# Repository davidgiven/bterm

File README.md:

bterm
=====

What?
-----

This is a set of firmware and hardware to turn a Brother WP-1 into a serial
terminal for a Raspberry Pi.

It consists of:

  - software to make a Brother bootable floppy containing a VT102-subset serial
	terminal

  - firmware for a PSoC5 CY8CKIT-049 based interface

  - a PCB which connects the Brother, CY8CKIT-049 and Raspberry Pi together

  - a 3D printable fascia which fits into the Brother's expansion slot

It also provides a MDA/Hercules/CGA-compatible video out connector which
reproduces what's on the Brother's screen.

Why?
----

Why not?

How?
----

So this is all so bespoke to my purposes that it's probably not going to be
very useful to anyone else. What documentation there is comes from the Youtube
series of videos I made while I developed this:

https://www.youtube.com/playlist?list=PLuQ2s_IbSWv5NDpc9Ew3BYDSF7siX9mNj

But here are some quick notes:

  - build the client software are write it to a floppy (you'll need zmac, ld80
	and fluxengine)

  - build the CY8CKIT-049 firmware and flash it with the Cypress development
	tools

  - get the PCB made and solder the connectors onto it

  - solder a 44-pin connector onto the unpopulated expansion breakout pads on
	the Brother motherboard

  - install Linux (or another OS of your choice) onto a Raspberry Pi, and
	configure out to use hardware handshaking on the main UART

  - plug everything together and attach the flyleads to the Brother CPU's /RD,
	/WR and /IOEN lines

  - ensure that there's a reset button and power switch connected to the
	interface board

  - switch everything on with Code+Q pressed on the Brother

...and then, if you're lucky, it might work.

If you are actually interested in trying this, best thing is to [file an
issue](https://github.com/davidgiven/bterm/issues/new/choose) and I'll see what
I can do to help. Or just send me an email (see below).

Who?
----

I am David Given, a.k.a. hjalfi in various places. Feel free to send me email
at [dg@cowlark.com](mailto:dg@cowlark.com). You may also [like to visit my
website](http://cowlark.com); there may or may not be something interesting
there.

License?
--------

Everything I wrote, which is nearly everything, is freely redistributable under
the terms of the simplified 2-clause BSD license. tl;dr: go nuts, just don't
claim you wrote it. See the `LICENSE` file for more details.

The one exception are the Raspberry Pi and CYC8KIT-049 footprints in the
`kicad-pcb` directory, which are by SnapEDA and licensed under a Creative
Commons Attribution-ShareAlike 4.0 International License (CC BY-SA) with Design
Exception 1.0. This exception essentially means that the CC BY-SA limitations
don't apply as they're being distributed as part of an aggregate design. [See
SnapEDA's page for
details.](https://support.snapeda.com/en/articles/2957815-what-is-the-design-exception-1-0)

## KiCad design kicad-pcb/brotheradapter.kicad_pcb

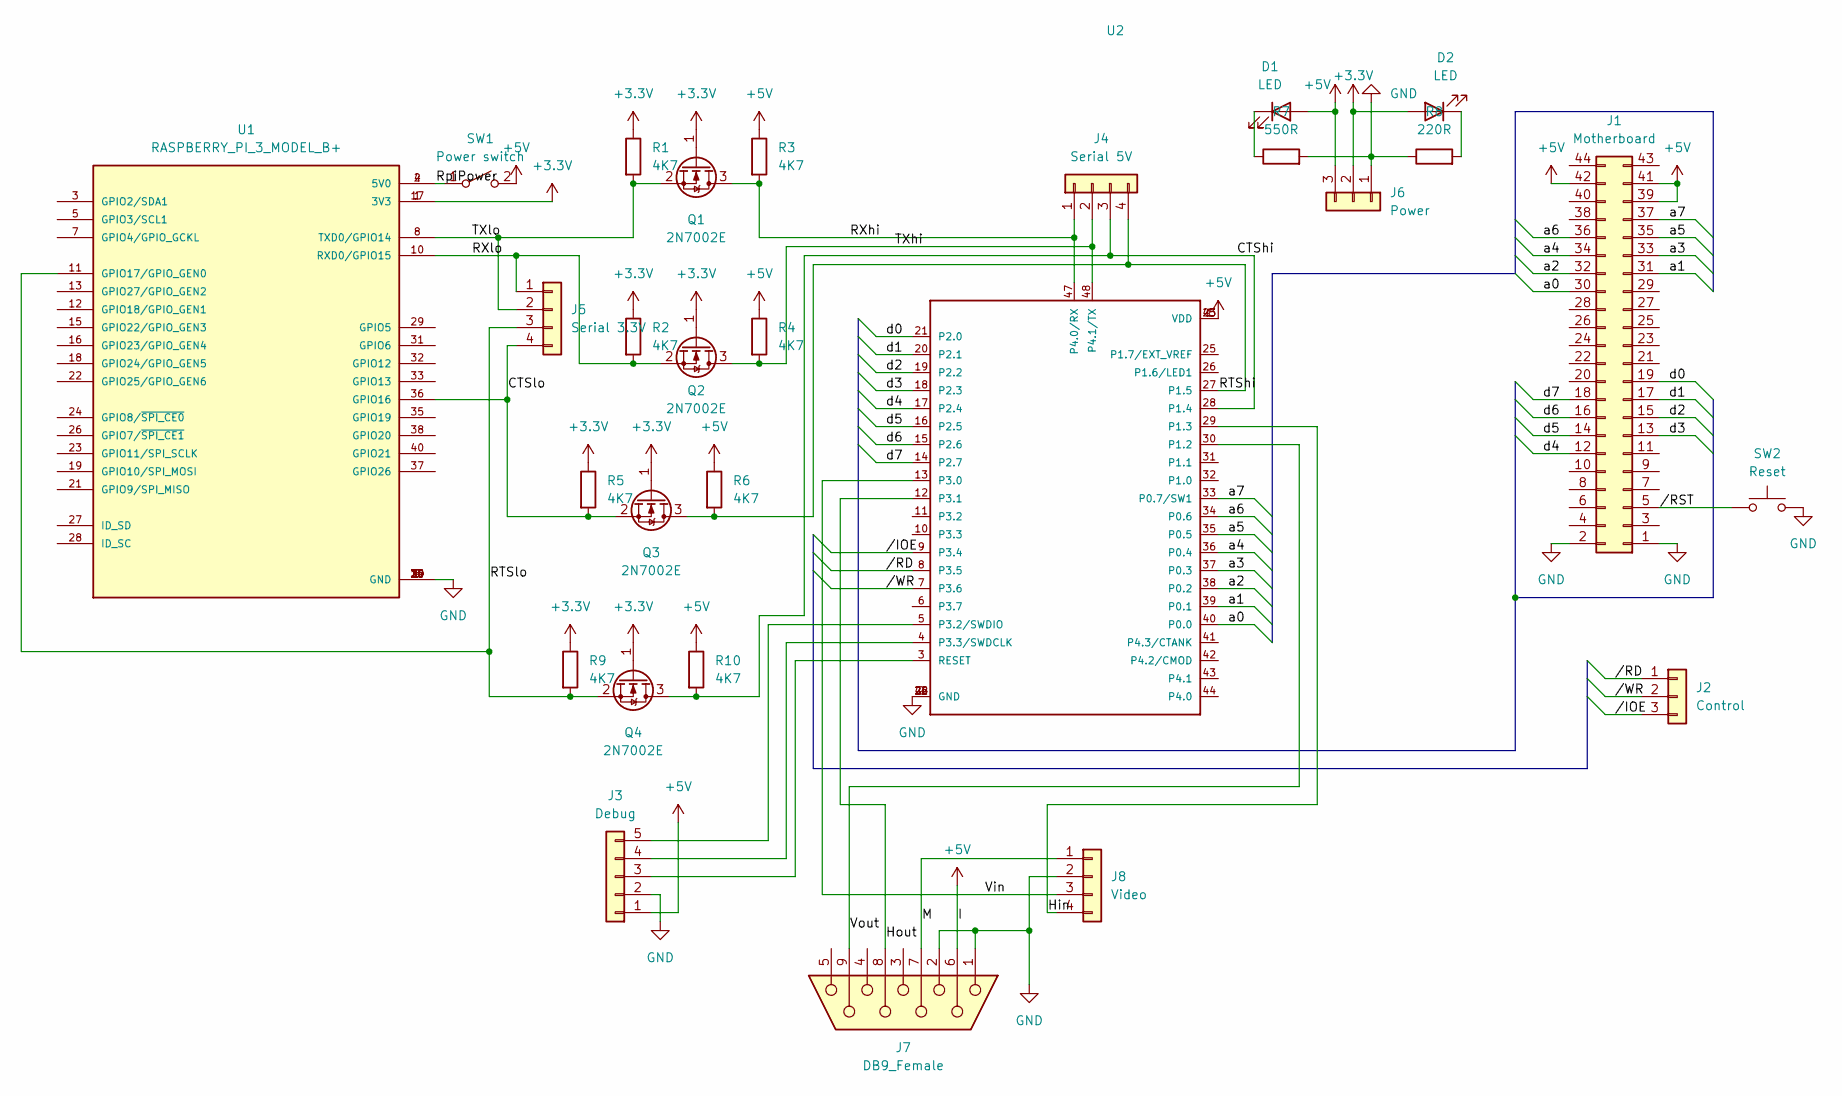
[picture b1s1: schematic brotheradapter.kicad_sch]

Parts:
D1, D2: LED; LED_0603_1608Metric
J1: Motherboard; PinHeader_2x22_P2.54mm_Vertical
J2: Control; PinSocket_1x03_P2.54mm_Vertical
J3: Debug; PinHeader_1x05_P2.54mm_Vertical
J4: Serial 5V; PinSocket_1x04_P2.54mm_Vertical
J5: Serial 3.3V; PinSocket_1x04_P2.54mm_Vertical
J6: Power; PinSocket_1x03_P2.54mm_Vertical
J7: DB9_Female; DSUB-9_Female_EdgeMount_P2.77mm
J8: Video; PinHeader_1x04_P2.54mm_Vertical
Q1, Q2, Q3, Q4: 2N7002E; SOT-23
R1, R2, R3, R4, R5, R6, R9, R10: 4K7; R_0603_1608Metric
R7: 550R; R_0603_1608Metric
R8: 220R; R_0603_1608Metric
SW1: Power switch; PinHeader_1x02_P2.54mm_Vertical
SW2: Reset; PinHeader_1x02_P2.54mm_Vertical
U1: RASPBERRY_PI_3_MODEL_B+; MODULE_RASPBERRY_PI_3_MODEL_B+; PARTREV 1.0
U2: CY8CKIT-049-42XX

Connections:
+3V3: D2.2 (A), J6.2, Q1.1 (G), Q2.1 (G), Q3.1 (G), Q4.1 (G), R1.1, R2.1, R5.1, R9.1, U1.1 (3V3), U1.17 (3V3)
+5V: D1.2 (A), J1.39, J1.41, J1.42, J3.1, J6.3, J7.6, R3.1, R4.1, R6.1, R10.1, SW1.2 (B), U2.1 (VDD), U2.23 (VDD), U2.45 (VDD)
/CTShi: J4.3, Q4.3 (D), R10.2, U2.28 (P1.4)
/CTSlo: J5.4, Q3.2 (S), R5.2, U1.36 (GPIO16)
/Hin: J8.4, U2.29 (P1.3)
/Hout: J7.8, U2.12 (P3.1)
/M: J7.7, J8.1
/RTSlo: J5.3, Q4.2 (S), R9.2, U1.11 (GPIO17/GPIO_GEN0)
/RXhi: J4.1, Q1.3 (D), R3.2, U2.47 (P4.0/RX)
/RXlo: J5.1, Q2.2 (S), R2.2, U1.10 (RXD0/GPIO15)
/RpiPower: SW1.1 (A), U1.2 (5V0), U1.4 (5V0)
/TXhi: J4.2, Q2.3 (D), R4.2, U2.48 (P4.1/TX)
/TXlo: J5.2, Q1.2 (S), R1.2, U1.8 (TXD0/GPIO14)
/Vin: J8.3, U2.13 (P3.0)
/Vout: J7.9, U2.30 (P1.2)
/a0: J1.30, U2.40 (P0.0)
/a1: J1.31, U2.39 (P0.1)
/a2: J1.32, U2.38 (P0.2)
/a3: J1.33, U2.37 (P0.3)
/a4: J1.34, U2.36 (P0.4)
/a5: J1.35, U2.35 (P0.5)
/a6: J1.36, U2.34 (P0.6)
/a7: J1.37, U2.33 (P0.7/SW1)
/d0: J1.19, U2.21 (P2.0)
/d1: J1.17, U2.20 (P2.1)
/d2: J1.15, U2.19 (P2.2)
/d3: J1.13, U2.18 (P2.3)
/d4: J1.12, U2.17 (P2.4)
/d5: J1.14, U2.16 (P2.5)
/d6: J1.16, U2.15 (P2.6)
/d7: J1.18, U2.14 (P2.7)
//IOE: J2.3, U2.9 (P3.4)
//RD: J2.1, U2.8 (P3.5)
//RST: J1.5, SW2.1
//WR: J2.2, U2.7 (P3.6)
GND: J1.1, J1.2, J3.2, J6.1, J7.1, J7.2, J8.2, R7.2, R8.1, SW2.2, U1.6 (GND), U1.9 (GND), U1.14 (GND), U1.20 (GND), U1.25 (GND), U1.30 (GND), U1.34 (GND), U1.39 (GND), U2.2 (GND), U2.22 (GND), U2.24 (GND), U2.46 (GND)
unnamed: D1.1 (K), R7.1
unnamed: D2.1 (K), R8.2
unnamed: J3.3, U2.3 (RESET)
unnamed: J3.4, U2.4 (P3.3/SWDCLK)
unnamed: J3.5, U2.5 (P3.2/SWDIO)
unnamed: J4.4, Q3.3 (D), R6.2, U2.27 (P1.5)

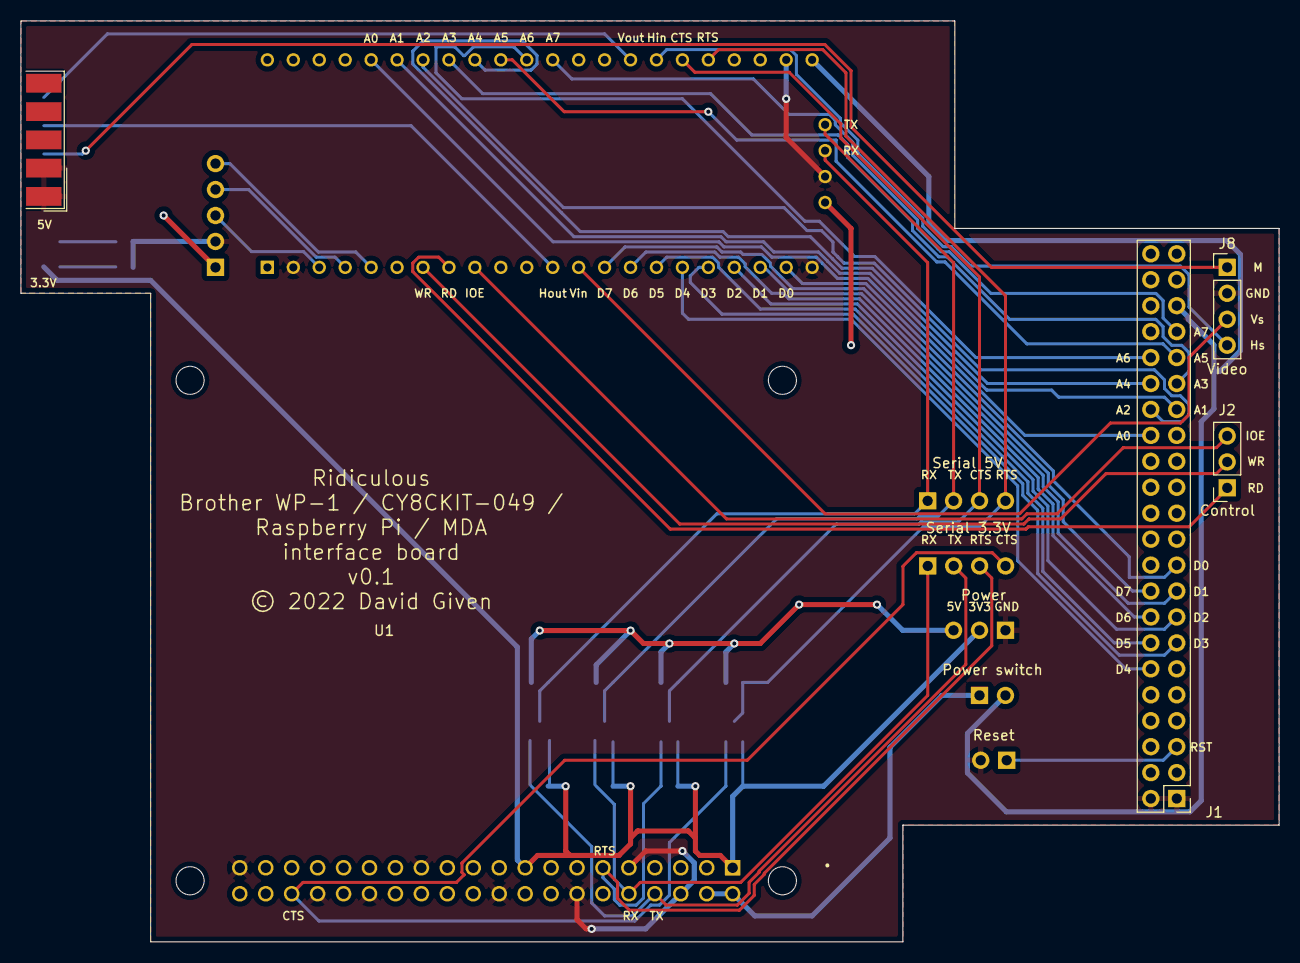
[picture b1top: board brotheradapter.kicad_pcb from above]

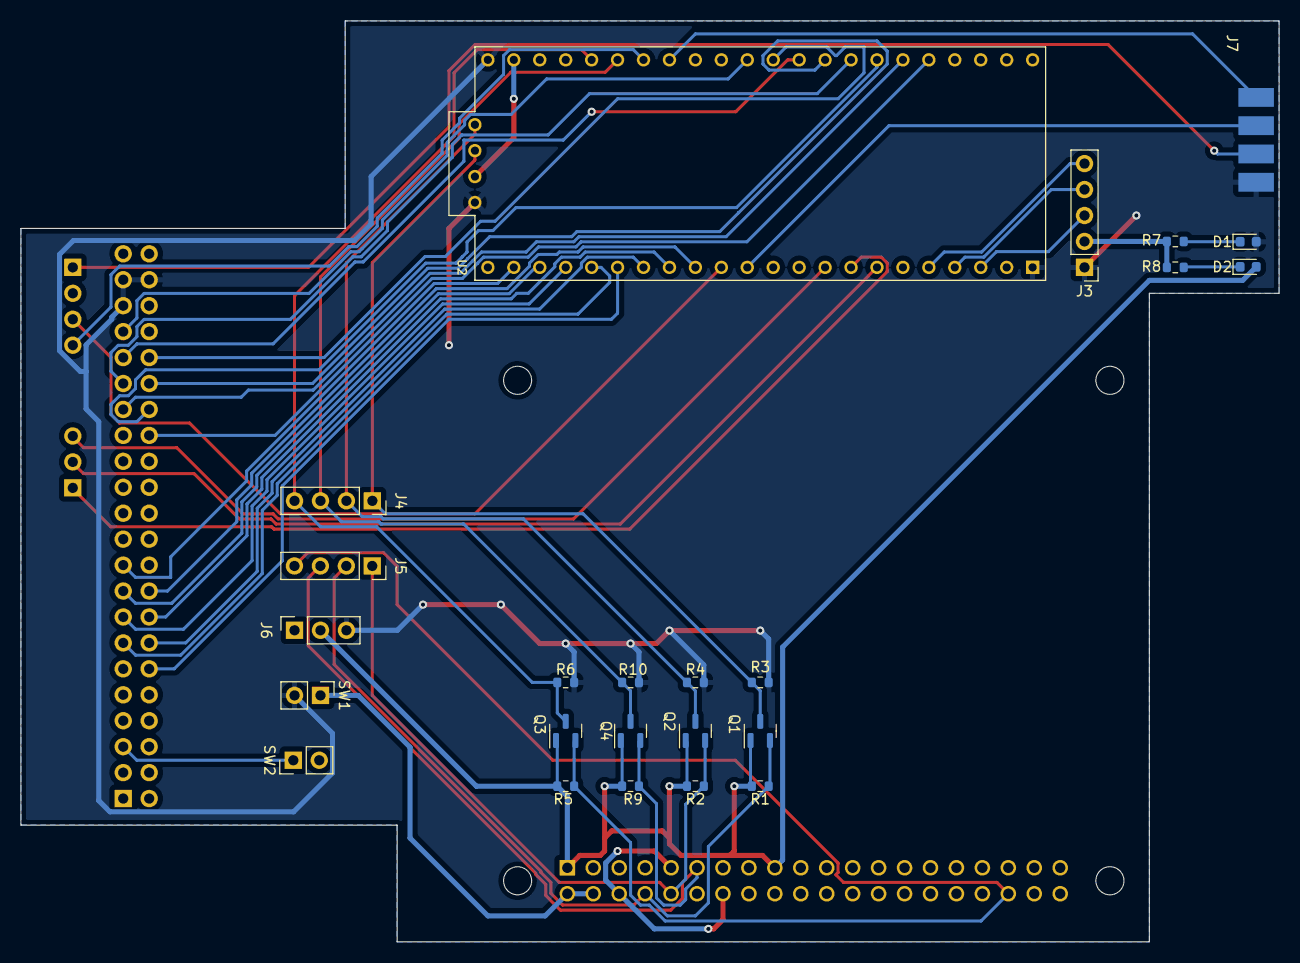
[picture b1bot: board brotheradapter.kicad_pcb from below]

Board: 2 copper layers, 123.2 x 90.2 mm, 28 parts (23 on the bottom side), 42 nets.

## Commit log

2022-04-24 Client is code complete.
2022-04-24 Stop using the out0a and in0a macros now we have proper z180 support.
2022-04-25 Lots of fixes --- most of the terminal now works.
2022-05-03 Import PSoC project.
2022-05-07 Invert hsync and vsync to make the OSSC happier.
2022-05-08 Lots of bug fixes and improvements.
2022-05-08 Fix bug where everything was being put at the wrong location in physical memory... with hilarious results.
2022-05-08 Use DMA for updating the screen. Pack rows close together in video memory so that STRIDE == WIDTH.
2022-05-08 Remove the per-line dirty stuff, instead using a simple round-robin of updates with a three frame cycle. Seems to work much better and is simpler.
2022-05-08 Add CTS pin, hopefully.
2022-05-09 Bump the baud rate to 115200 and make CTS work.
2022-05-10 Add support for attributes. Use DMA for copying memory (almost) everywhere.
2022-05-11 Make delete-to-start-of-line work.
2022-05-11 Turn jps into jrs.
2022-05-11 Fix UTF-8 parsing.
2022-05-12 Most of ISO-8859-1 works, and just enough box drawing characters for WordGrinder.
2022-05-12 Switch to four-page updates rather than three to remove the last bit of snow.
2022-05-12 Typo fix.
2022-05-23 Move the video pins to the right place for the bespoke PCB.
2022-05-24 Update some more pin assignments.
2022-05-26 Fix pin assignments, again.
2022-07-07 Initial version of jif.
2022-07-07 Convert vt102 to use jif; improve jif a lot.
2022-07-07 Responsiveness fixes --- now the area under the cursor is refreshed first after an update.
2022-07-08 Fix OBO error when inserting and deleting lines.
2022-07-08 Add the kicad PCB.
2022-07-08 Add the fascia SolveSpace model.
2022-07-08 Populate README.
2022-07-08 Fix formatting.

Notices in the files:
kicad-pcb/brotheradapter.kicad_pcb:
© 2022 David Given
